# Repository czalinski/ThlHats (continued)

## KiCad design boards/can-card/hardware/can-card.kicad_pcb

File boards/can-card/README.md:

# CAN card: 4 isolated CAN FD

Daughter card in the core's stack (docs/requirements.md 4.5).

- Board: 100 x 100 mm, 2 layers, rev A
- Mounting: 4x M4 stack holes (tools/stack_bus.py), no Pi header
- Stack: J10 logic bus (C1-C4 TX/RX, +3V3, +5V, GND), J11 rack power (+12V,
  GND_RACK, only for CAN1 POWERED); Samtec ESQ stacking sockets on top
- Channels: TI ISOW1044B (basic isolation; ISOW1044 reinforced also fits) each (integrated isolated DC-DC), every bus ground
  floating; MC 1,5/4 terminals: 1 CANH, 2 CANL, 3 GND, 4 +12 V (CAN1 only)
- Jumpers: JP1-JP4 120 R termination; JP5 + JP6 CAN1 POWERED (ties GND_CAN1
  to GND_RACK, feeds +12 V through F10)
- MCU: none (the core's PIC32MK drives the CAN lines)

**Rev B:** each ISOW1044 is replaced by a TI ISO1042 transceiver plus an
isolated 5 V supply (SN6505B, Würth 760390014, LP2985A-50), because the
ISOW1044 and ISOW1044B were out of stock for rev A; rev A can-cards are not
built. See docs/rev-b-changes.md.

## Layout

- `hardware/` KiCad project
  - `gen_schematic.py` bootstrap schematic generator (stop once edited in KiCad)
  - `place.py` outline, holes, placement, domain pours, isolation gaps, TI keep-outs
  - `route.py` routing pipeline (`all` = delete tracks, place, pre, Freerouting, finish)
- `firmware/` none (no MCU on this card)

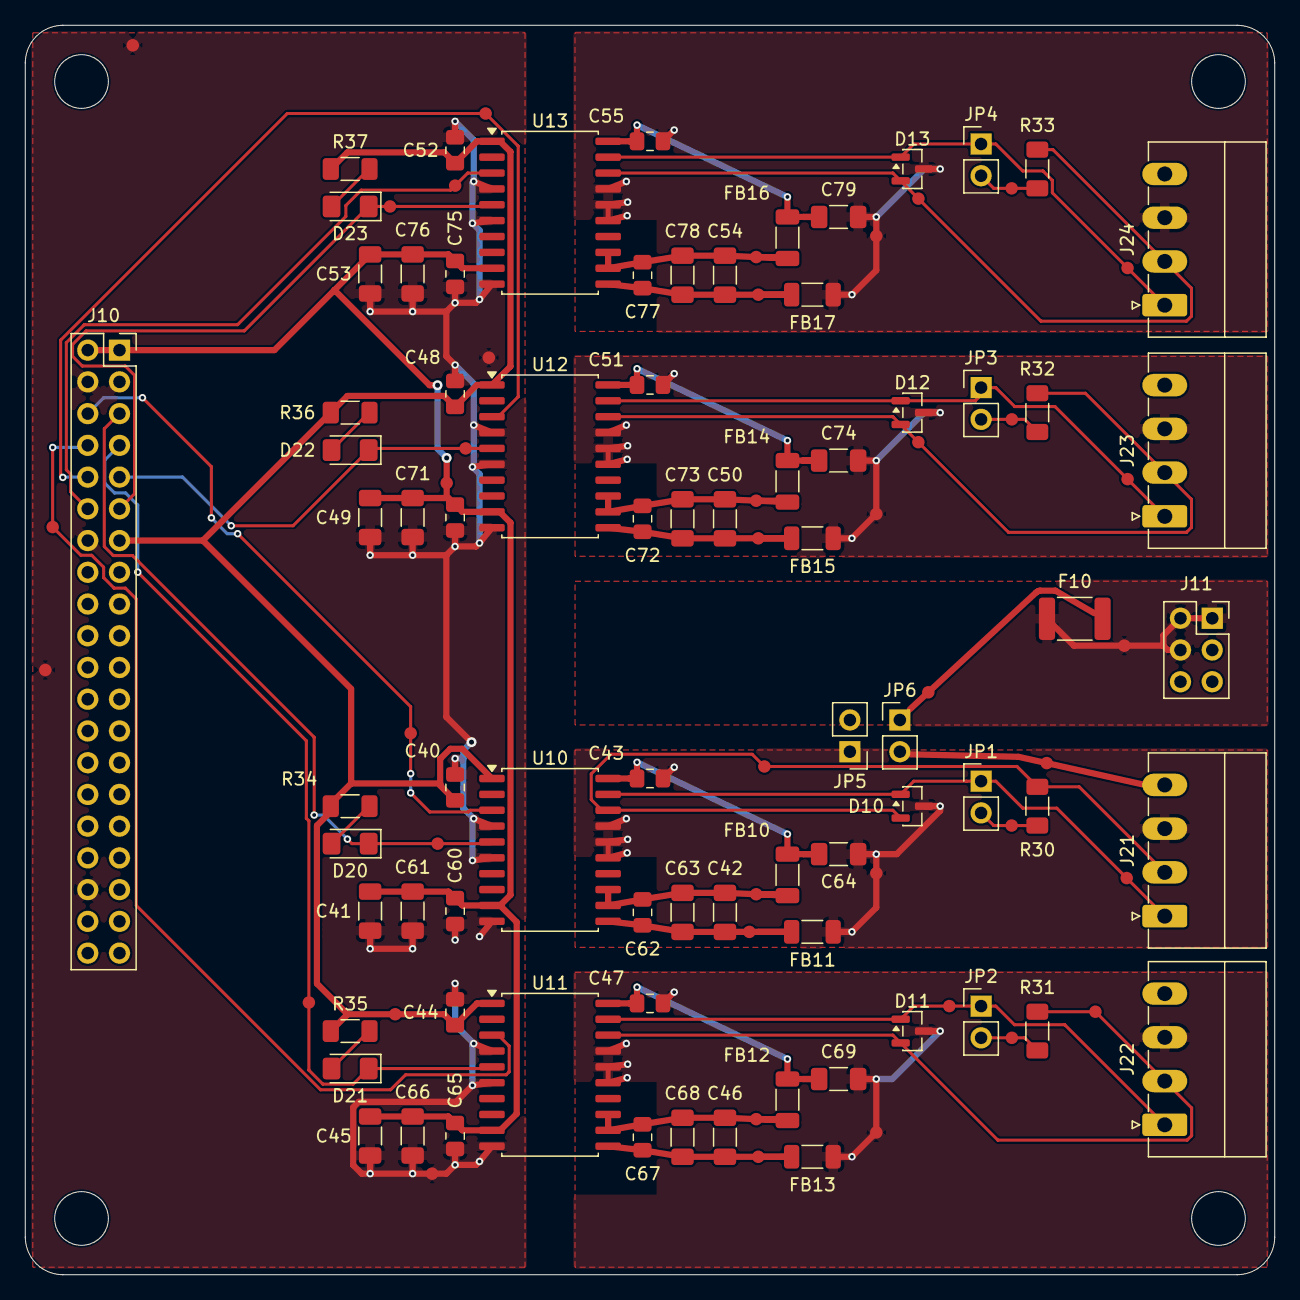
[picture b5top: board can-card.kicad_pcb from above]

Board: 2 copper layers, 100.0 x 100.0 mm, 122 parts (0 on the bottom side), 47 nets.

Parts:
C40, C43, C44, C47, C48, C51, C52, C55: 100nF 50V X7R; C_0805_2012Metric_Pad1.18x1.45mm_HandSolder
C41, C42, C45, C46, C49, C50, C53, C54, C64, C69, C74, C79: 10uF 25V X7R; C_1206_3216Metric_Pad1.33x1.80mm_HandSolder
C60, C62, C65, C67, C70, C72, C75, C77: 10nF 50V X7R; C_0805_2012Metric_Pad1.18x1.45mm_HandSolder
C61, C63, C66, C68, C71, C73, C76, C78: 1uF 50V X7R; C_1206_3216Metric_Pad1.33x1.80mm_HandSolder
D10, D11, D12, D13: NUP2105L; SOT-23
D20, D21, D22, D23: LED yellow; LED_1206_3216Metric_Pad1.42x1.75mm_HandSolder
F10: 2A; Fuse_1812_4532Metric_Pad1.30x3.40mm_HandSolder
FB10, FB11, FB12, FB13, FB14, FB15, FB16, FB17: BLM31PG391SN1L; L_1206_3216Metric_Pad1.22x1.90mm_HandSolder
J10: STACK BUS; PinSocket_2x20_P2.54mm_Vertical
J11: RACK 12V; PinSocket_2x03_P2.54mm_Vertical
J21: CAN1; PhoenixContact_MC_1,5_4-G-3.5_1x04_P3.50mm_Horizontal
J22: CAN2; PhoenixContact_MC_1,5_4-G-3.5_1x04_P3.50mm_Horizontal
J23: CAN3; PhoenixContact_MC_1,5_4-G-3.5_1x04_P3.50mm_Horizontal
J24: CAN4; PhoenixContact_MC_1,5_4-G-3.5_1x04_P3.50mm_Horizontal
JP1, JP2, JP3, JP4: TERM; PinHeader_1x02_P2.54mm_Vertical
JP5: POWERED GND; PinHeader_1x02_P2.54mm_Vertical
JP6: POWERED 12V; PinHeader_1x02_P2.54mm_Vertical
MH1, MH2, MH3, MH4: MountingHole_4.3mm_M4_Standoff7mm
R30, R31, R32, R33: 120R; R_1206_3216Metric_Pad1.30x1.75mm_HandSolder
R34, R35, R36, R37: 1k; R_1206_3216Metric_Pad1.30x1.75mm_HandSolder
TP1, TP10, TP22: pour; TP_Probe_D1.0mm
TP2, TP3, TP4, TP5, TP6, TP7, TP8, TP9, TP11, TP12, TP13, TP14, TP15, TP16, TP17, TP18, TP19, TP20, TP21, TP23, TP24, TP25, TP26, TP27, TP28, TP29, TP30, TP31, TP32, TP33, TP34, TP35, TP36, TP37, TP38, TP39, TP40, TP41: track; TP_Probe_D1.0mm
U10, U11, U12, U13: ISOW1044B; SOIC-20W_7.5x12.8mm_P1.27mm

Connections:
+3V3: C40.1, C44.1, C48.1, C52.1, J10.13, R34.1, R35.1, R36.1, R37.1, TP33.1, U10.1, U11.1, U12.1, U13.1
+5V: C41.1, C45.1, C49.1, C53.1, C60.1, C61.1, C65.1, C66.1, C70.1, C71.1, C75.1, C76.1, J10.1, J10.2, TP12.1, U10.9, U11.9, U12.9, U13.9
+12V: F10.1, J11.1, J11.2, J11.4, TP21.1
/C1RX: D20.1, J10.5, TP27.1, U10.5
/C1TX: J10.6, TP23.1, U10.3
/C2RX: D21.1, J10.7, TP32.1, U11.5
/C2TX: J10.8, TP19.1, U11.3
/C3RX: D22.1, J10.9, TP13.1, U12.5
/C3TX: J10.10, TP2.1, U12.3
/C4RX: D23.1, J10.11, TP3.1, U13.5
/C4TX: J10.12, TP4.1, U13.3
/CANH1: D10.1, J21.1, JP1.1, TP31.1, U10.19
/CANH2: D11.1, J22.1, JP2.1, TP35.1, U11.19
/CANH3: D12.1, J23.1, JP3.1, TP18.1, U12.19
/CANH4: D13.1, J24.1, JP4.1, TP9.1, U13.19
/CANL1: D10.2, J21.2, R30.2, TP24.1, U10.18
/CANL2: D11.2, J22.2, R31.2, TP36.1, U11.18
/CANL3: D12.2, J23.2, R32.2, TP16.1, U12.18
/CANL4: D13.2, J24.2, R33.2, TP7.1, U13.18
/D20_A: D20.2, R34.2
/D21_A: D21.2, R35.2
/D22_A: D22.2, R36.2
/D23_A: D23.2, R37.2
/GND2_1: C42.2, C62.2, C63.2, FB11.1, TP34.1, U10.11
/GND2_2: C46.2, C67.2, C68.2, FB13.1, TP41.1, U11.11
/GND2_3: C50.2, C72.2, C73.2, FB15.1, TP20.1, U12.11
/GND2_4: C54.2, C77.2, C78.2, FB17.1, TP11.1, U13.11
/GND_CAN1: C43.2, C64.2, D10.3, FB11.2, J21.3, JP5.1, TP29.1, U10.15, U10.16, U10.17
/GND_CAN2: C47.2, C69.2, D11.3, FB13.2, J22.3, TP38.1, U11.15, U11.16, U11.17
/GND_CAN3: C51.2, C74.2, D12.3, FB15.2, J23.3, TP15.1, U12.15, U12.16, U12.17
/GND_CAN4: C55.2, C79.2, D13.3, FB17.2, J24.3, TP6.1, U13.15, U13.16, U13.17
/GND_RACK: J11.3, J11.5, J11.6, JP5.2
/TERM1: JP1.2, R30.1, TP30.1
/TERM2: JP2.2, R31.1, TP39.1
/TERM3: JP3.2, R32.1, TP17.1
/TERM4: JP4.2, R33.1, TP8.1
/V12_CAN1: J21.4, JP6.2, TP26.1
/V12_F10: F10.2, JP6.1, TP25.1
/VCAN1: C43.1, C64.1, FB10.2, U10.20
/VCAN2: C47.1, C69.1, FB12.2, U11.20
/VCAN3: C51.1, C74.1, FB14.2, U12.20
/VCAN4: C55.1, C79.1, FB16.2, U13.20
/VISO1: C42.1, C62.1, C63.1, FB10.1, TP28.1, U10.12, U10.13
/VISO2: C46.1, C67.1, C68.1, FB12.1, TP37.1, U11.12, U11.13
/VISO3: C50.1, C72.1, C73.1, FB14.1, TP14.1, U12.12, U12.13
/VISO4: C54.1, C77.1, C78.1, FB16.1, TP5.1, U13.12, U13.13
GND: C40.2, C41.2, C44.2, C45.2, C48.2, C49.2, C52.2, C53.2, C60.2, C61.2, C65.2, C66.2, C70.2, C71.2, C75.2, C76.2, J10.3, J10.4, J10.14, J10.36, TP1.1, TP10.1, TP22.1, TP40.1, U10.4, U10.6, U10.10, U11.4, U11.6, U11.10, U12.4, U12.6, U12.10, U13.4, U13.6, U13.10

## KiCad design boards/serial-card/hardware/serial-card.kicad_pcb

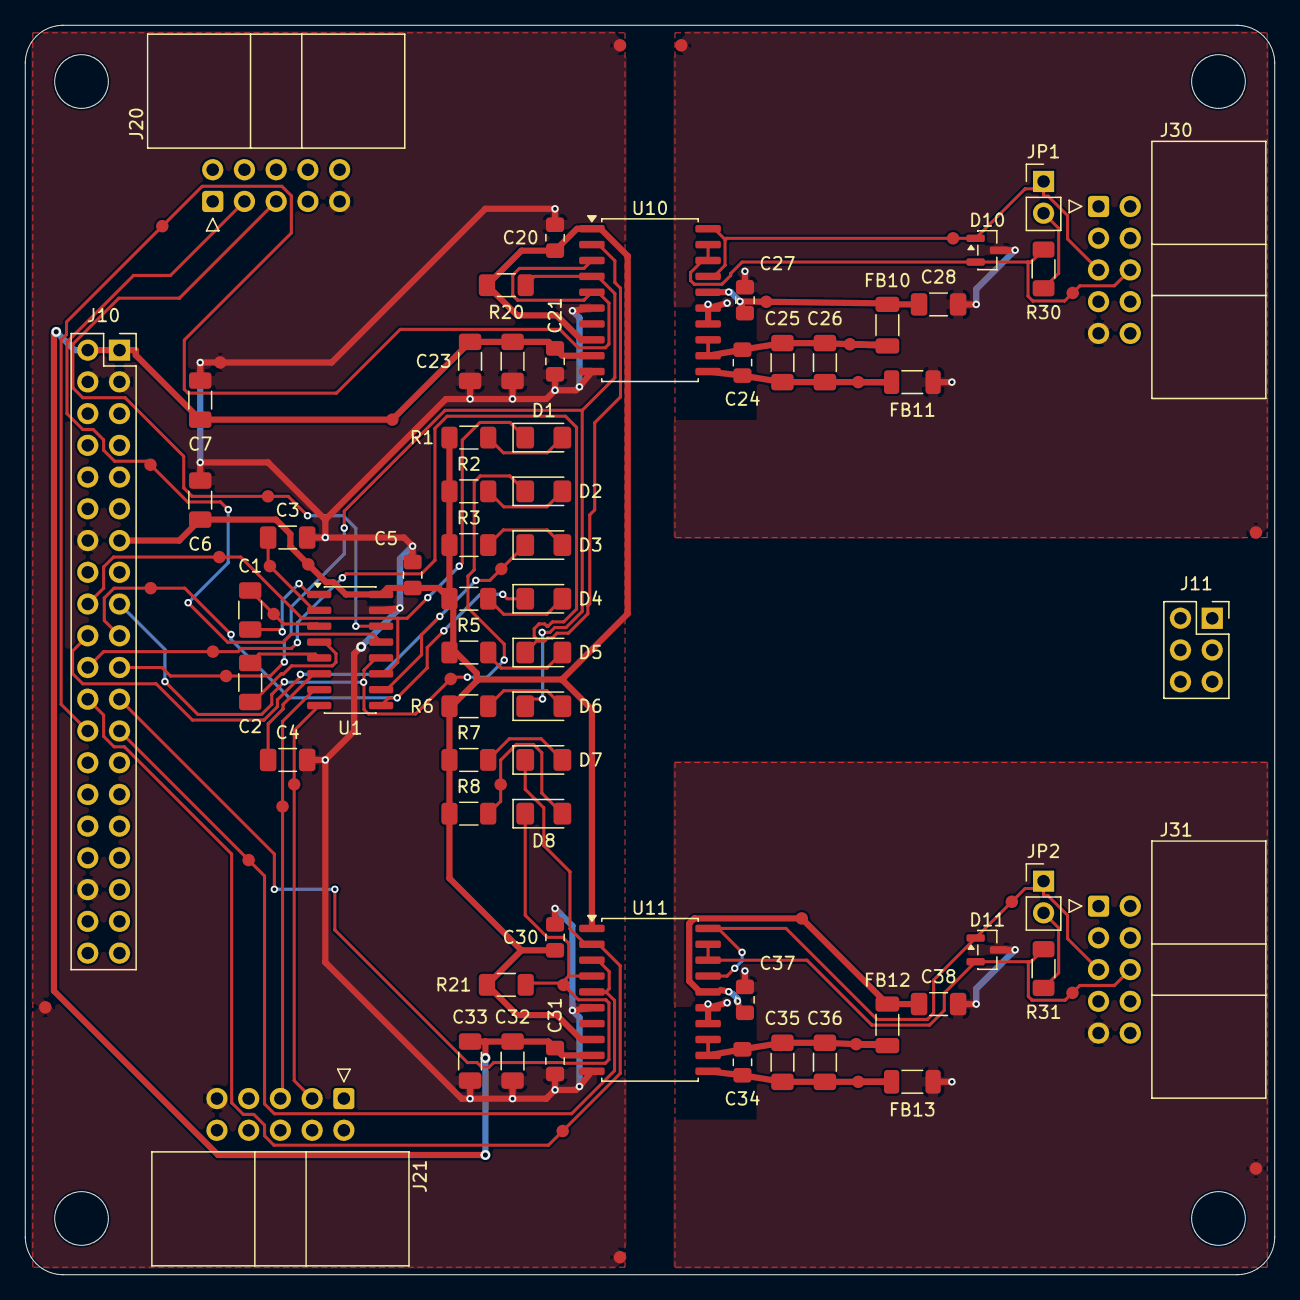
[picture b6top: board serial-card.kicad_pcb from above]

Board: 2 copper layers, 100.0 x 100.0 mm, 102 parts (0 on the bottom side), 45 nets.

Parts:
C1, C2, C3, C4: 100nF 50V X7R; C_1206_3216Metric_Pad1.33x1.80mm_HandSolder
C5, C20, C27, C30, C37: 100nF 50V X7R; C_0805_2012Metric_Pad1.18x1.45mm_HandSolder
C6, C7, C23, C26, C28, C33, C36, C38: 10uF 25V X7R; C_1206_3216Metric_Pad1.33x1.80mm_HandSolder
C21, C24, C31, C34: 10nF 50V X7R; C_0805_2012Metric_Pad1.18x1.45mm_HandSolder
C22, C25, C32, C35: 1uF 50V X7R; C_1206_3216Metric_Pad1.33x1.80mm_HandSolder
D1, D3, D5, D7: LED green; LED_1206_3216Metric_Pad1.42x1.75mm_HandSolder
D2, D4, D6, D8: LED yellow; LED_1206_3216Metric_Pad1.42x1.75mm_HandSolder
D10, D11: SM712; SOT-23
FB10, FB11, FB12, FB13: BLM31PG391SN1L; L_1206_3216Metric_Pad1.22x1.90mm_HandSolder
J10: STACK BUS; PinSocket_2x20_P2.54mm_Vertical
J11: RACK 12V; PinSocket_2x03_P2.54mm_Vertical
J20: RS-232 1; Amphenol_T821110A1R100CEU_2x05_P2.54mm_Horizontal
J21: RS-232 2; Amphenol_T821110A1R100CEU_2x05_P2.54mm_Horizontal
J30: RS-485 3; Amphenol_T821110A1R100CEU_2x05_P2.54mm_Horizontal
J31: RS-485 4; Amphenol_T821110A1R100CEU_2x05_P2.54mm_Horizontal
JP1, JP2: TERM; PinHeader_1x02_P2.54mm_Vertical
MH1, MH2, MH3, MH4: MountingHole_4.3mm_M4_Standoff7mm
R1, R2, R3, R4, R5, R6, R7, R8: 1k; R_1206_3216Metric_Pad1.30x1.75mm_HandSolder
R20, R21: 10k; R_1206_3216Metric_Pad1.30x1.75mm_HandSolder
R30, R31: 120R; R_1206_3216Metric_Pad1.30x1.75mm_HandSolder
TP1, TP2, TP19, TP27, TP35, TP36: pour; TP_Probe_D1.0mm
TP3, TP4, TP5, TP6, TP7, TP8, TP9, TP10, TP11, TP12, TP13, TP14, TP15, TP16, TP17, TP18, TP20, TP21, TP22, TP23, TP24, TP25, TP26, TP28, TP29, TP30, TP31, TP32, TP33, TP34: track; TP_Probe_D1.0mm
U1: ST3232B; SOIC-16_3.9x9.9mm_P1.27mm
U10, U11: ISOW1432; SOIC-20W_7.5x12.8mm_P1.27mm

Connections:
+3V3: C5.1, C6.1, C20.1, C30.1, J10.13, R1.1, R2.1, R3.1, R4.1, R5.1, R6.1, R7.1, R8.1, R20.1, R21.1, TP17.1, U1.16, U10.1, U10.8, U11.1, U11.8
+5V: C7.1, C21.1, C22.1, C23.1, C31.1, C32.1, C33.1, J10.1, J10.2, TP12.1, U10.9, U11.9
/C1N: C1.2, TP16.1, U1.3
/C1P: C1.1, U1.1
/C2N: C2.2, U1.5
/C2P: C2.1, U1.4
/D1_A: D1.2, R1.2
/D2_A: D2.2, R2.2
/D3_A: D3.2, R3.2
/D4_A: D4.2, R4.2
/D5_A: D5.2, R5.2
/D6_A: D6.2, R6.2
/D7_A: D7.2, R7.2
/D8_A: D8.2, R8.2, TP26.1
/DE1: J10.26, TP3.1, U10.3, U10.5
/DE2: J10.25, TP23.1, U11.3, U11.5
/DN3: D10.2, J30.6, R30.2, TP9.1, U10.18, U10.19
/DN4: D11.2, J31.6, R31.2, TP31.1, U11.18, U11.19
/DP3: D10.1, J30.5, JP1.1, TP4.1, U10.17, U10.20
/DP4: D11.1, J31.5, JP2.1, TP30.1, U11.17, U11.20
/GND2_3: C24.2, C25.2, C26.2, FB11.1, TP8.1, U10.11
/GND2_4: C34.2, C35.2, C36.2, FB13.1, TP34.1, U11.11
/GND_485_3: C27.2, C28.2, D10.3, FB11.2, J30.9, TP2.1, TP19.1, U10.14, U10.15
/GND_485_4: C37.2, C38.2, D11.3, FB13.2, J31.9, TP36.1, U11.14, U11.15
/RXD1: J20.3, TP10.1, U1.13
/RXD2: J21.3, TP25.1, U1.8
/TERM3: JP1.2, R30.1
/TERM4: JP2.2, R31.1
/TXD1: J20.5, TP11.1, U1.14
/TXD2: J21.5, TP24.1, U1.7
/U2RX: D2.1, J10.17, TP22.1, U1.12
/U2TX: D1.1, J10.18, TP14.1, U1.11
/U3RX: D4.1, J10.19, TP13.1, U1.9
/U3TX: D3.1, J10.20, TP18.1, U1.10
/U4RX: D6.1, J10.21, R20.2, TP21.1, U10.4
/U4TX: D5.1, J10.22, TP20.1, U10.2
/U5RX: D8.1, J10.23, R21.2, TP28.1, U11.4
/U5TX: D7.1, J10.24, TP32.1, U11.2
/V485_3: C27.1, C28.1, FB10.2, TP6.1, U10.16
/V485_4: C37.1, C38.1, FB12.2, TP29.1, U11.16
/VISO3: C24.1, C25.1, C26.1, FB10.1, TP7.1, U10.12, U10.13
/VISO4: C34.1, C35.1, C36.1, FB12.1, TP33.1, U11.12, U11.13
/VSN: C4.1, U1.6
/VSP: C3.1, TP15.1, U1.2
GND: C3.2, C4.2, C5.2, C6.2, C7.2, C20.2, C21.2, C22.2, C23.2, C30.2, C31.2, C32.2, C33.2, J10.3, J10.4, J10.14, J10.36, J20.9, J21.9, TP1.1, TP5.1, TP27.1, TP35.1, U1.15, U10.6, U10.10, U11.6, U11.10

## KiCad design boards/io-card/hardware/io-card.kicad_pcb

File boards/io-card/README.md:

# IO card: relays, GPIO, differential AI, analog out

The "LabJack light" daughter card in the core's stack (docs/requirements.md
4.1 and 4.5). It has no MCU: the core's PIC32MK drives RLY1-4 and GPIO1-4 and
reads the analog legs on its ADC through the stack bus, and sets the analog
outputs over the bus's I2C1.

- Board: 100 x 100 mm, 2 layers, rev A.
- Mounting: 4x M4 stack holes (tools/stack_bus.py), no Pi header
  (`board.json` opts out).
- Stack: J10 logic bus (left edge) and J11 rack power (right edge), Samtec
  ESQ stacking sockets on top, as on the can-card. Every part stays under the
  next card, about 11 mm up (ESQ-120-14 body).

| Block | Circuit | Terminal |
|---|---|---|
| Relay drivers 1-4 | Drive **external** relay coils. 2 × Panasonic AQW212 PhotoMOS. The LED side runs on LOGIC: RLYn → 470R → LED. The contacts source V_RLY to OUTn, and the coil returns to 0 V next to it. Coil supply on JP1: 1-2 = rack +12 V (J11), 2-3 = external supply up to 24 V on J30 9/10. Both go through F30 (1.1 A, 33 V). Each output has a 1N4148W flyback diode and a red LED. The failsafe timeout is set by the host per `RLY` command and enforced by the core firmware. | **J30** bottom edge, MC 1,5/10-G-3,5: 1/2 OUT1 / 0 V … 7/8 OUT4 / 0 V, 9/10 external coil supply + / 0 V |
| GPIO 1-4 | 3.3 V straight from core pins, with 330R in series and a BAT54S clamp. Not 24 V tolerant. | **J40** top edge, MC 1,5/12-G-3,5: 1/2 IO1 / GND … 7/8 IO4 / GND |
| AO 1-4 (2026-10-10) | 0-10 V, 10 mA each, in the RACK domain: powered from rack +12 V, 0 V = GND_RACK (shared by all four and the relay returns). I2C1 from the bus crosses U90 (ISO1540) to U92 (MCP4728 quad 12-bit DAC at 0x60, internal 2.048 V reference x 2), then U93 (OPA4171) x 2.5 = 10.24 V full scale. 47R inside the loop (feedback from the terminal side) + 1 nF from the amplifier output for cable capacitance; BAT54S clamp to +12V / GND_RACK. U91 (MC78L05) makes 5 V for the DAC and the isolator's rack side. Needs the rack supply at 11 V or more for 10 V at 10 mA. | **J50** right edge, MC 1,5/8-G-3,5: 1/2 AO1 / 0 V … 7/8 AO4 / 0 V |
| AI 1-2 | Differential, ±116 V per input, 10 MΩ per input. Each leg is 10M / 130k to VMID_F, with 100 nF across the 130k and a BAT54S clamp. The core subtracts the two legs. VMID from the core arrives through R88 1k + C85 100 nF (VMID_F), because the core's OA5 is rated for only 32 pF of load. | J40 9/10 AI1+ / AI1-, 11/12 AI2+ / AI2- |

Plugs: Phoenix FMC 1,5/10-ST-3,5 and FMC 1,5/12-ST-3,5 (push-in, 7.8 mm).
The MC headers are 7.7 mm tall. The double-level SPTD terminals from the
first schematic are 24.2 mm tall and do not fit in the stack.

## Layout

- LOGIC: the top band (J40, GPIO clamps, AI dividers) and the left side
  (J10, decoupling, relay LED resistors).
- RACK: the lower-right block (J11, JP1, F30, C70/C71, flyback diodes, LEDs,
  J30).
- RACK also takes the top-right corner (x > 61.5 mm) for the analog outputs:
  the isolator, U91-U93, each channel's parts in a row beside its J50 pair.
- K1/K2 and U90 straddle a 2 mm copper-free gap on both layers. They are
  the only LOGIC | RACK crossings (1500 Vrms and 2500 Vrms, functional
  isolation).
- Ground pours on both layers in each domain.
- The AI terminal nets (`/AIN*`) are in net class HV, with a 0.8 mm
  clearance (IPC-2221B B4 needs 0.6 mm for 101-150 V).
- The MCP4728's nets are in net class Fine (0.2 mm tracks, 0.15 mm
  clearance) and a DRC rule allows its 0.15 mm pad gaps (MSOP-10, 0.5 mm
  pitch). Its pins and the four DAC-to-amplifier connections are routed by
  `route.py` (`dac_fanout`); Freerouting did not get through the pitch
  reliably.

## Build files

- `hardware/gen_schematic.py`: generates the schematic (A2 sheet: the
  analog outputs are in the band below the original A3 area). Stop using it
  once the schematic is edited in KiCad.
- `hardware/place.py`: outline, holes, placement, pours and the isolation
  gap. It can be rerun and leaves tracks alone.
- `hardware/route.py pre|auto|finish|all`: ground fan-out, Freerouting, then
  finishing. **Do not rerun `pre` or `all` on a hand-edited board**: they
  start over. `route.py ao` routed the analog outputs onto the routed board:
  it locks the existing tracks, fans out the new ground pads, pre-routes the
  DAC, runs Freerouting, removes the fragments Freerouting leaves on
  already-routed nets, and unlocks. Freerouting is not deterministic; check
  DRC after each run.

## Status (2026-10-10)

Analog outputs added: schematic, placement and routing. `tools/check_board.py`
is clean (ERC, DRC with schematic parity). The original routing is
unchanged, track for track. Core firmware 0.5 has the `AO` command
(boards/core/firmware/PROTOCOL.md); not yet tested on hardware.

## Status (2026-10-09)

Placed and routed. `tools/check_board.py` is clean: ERC, DRC and schematic
parity, with no warnings. References were tidied with `tools/silk_tidy.py`; D57's appears on the Fab layer only, because there was no clear silkscreen spot.
Next: io-card commands in the core firmware (RLY, GPIO, AI, and OA5 for
VMID).

Open items:

- Confirm the mated FMC plug height against the stack on the Phoenix
  drawing.
- There is no reverse-polarity protection on the external coil supply. If
  it is reversed, an output that is on lets its flyback diode short the
  supply through F30, which trips. Outputs that are off block it: the
  AQW212 is the GU AC/DC type (back-to-back MOSFETs; checked 2026-10-11).

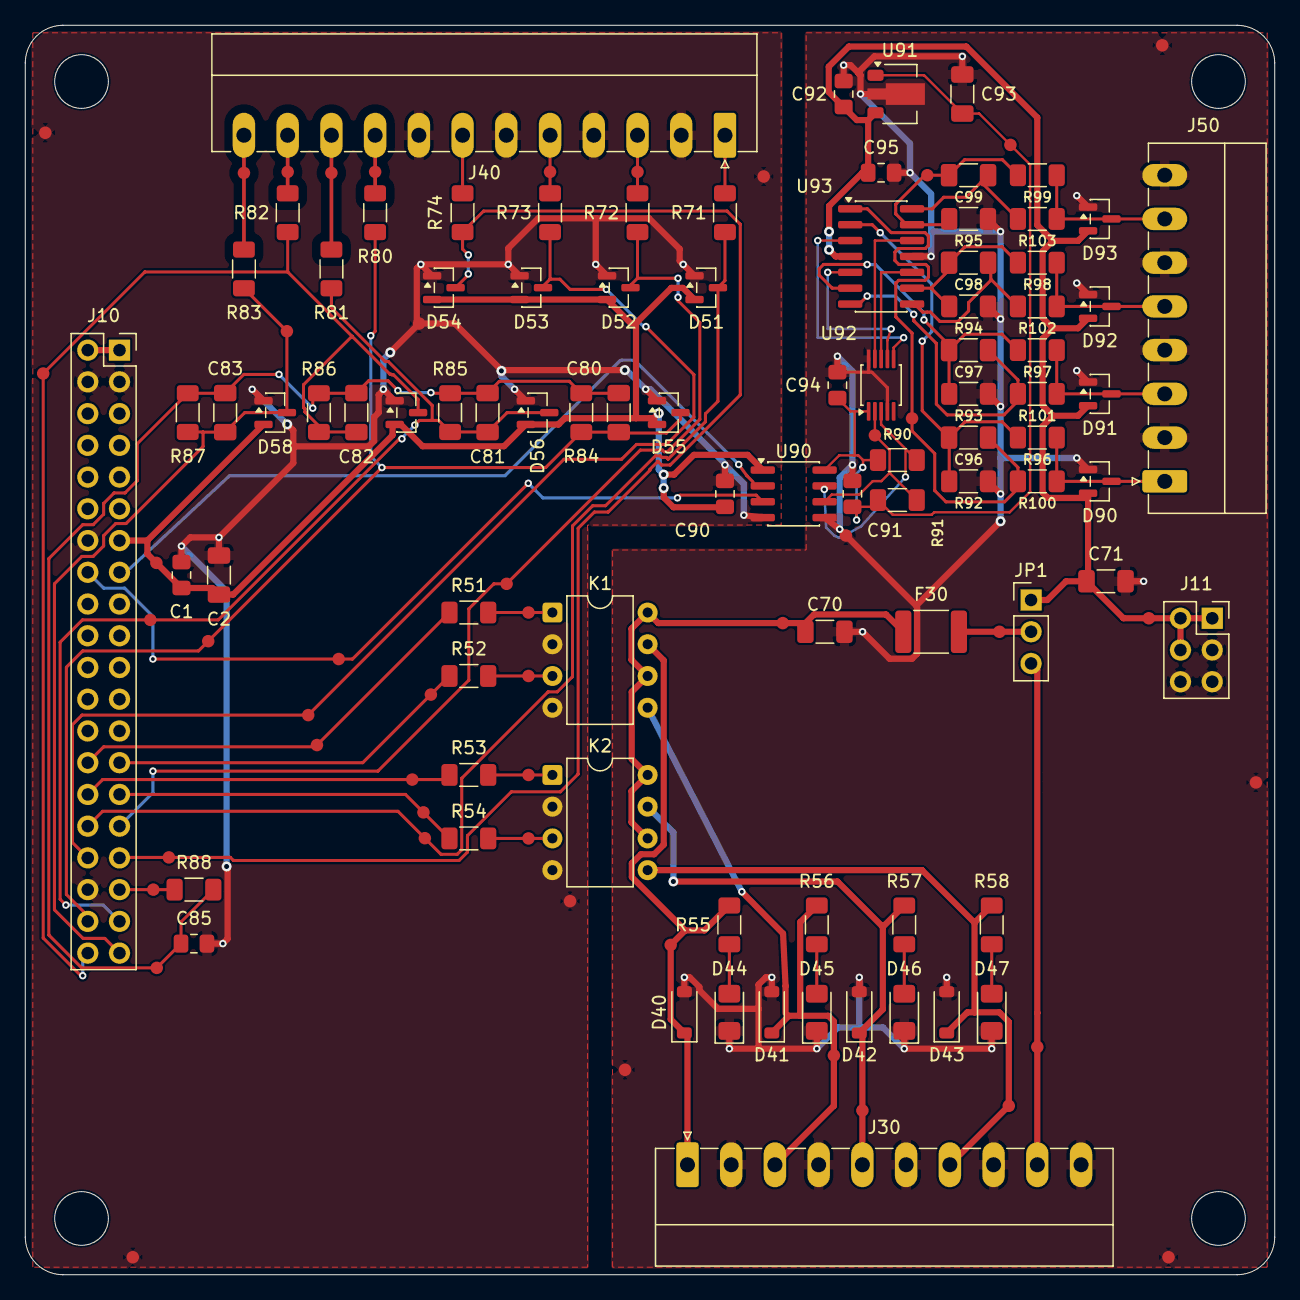
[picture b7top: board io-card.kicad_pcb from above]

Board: 2 copper layers, 100.0 x 100.0 mm, 139 parts (0 on the bottom side), 63 nets.

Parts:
C1, C85, C90, C91, C92, C94, C95: 100nF 50V X7R; C_0805_2012Metric_Pad1.18x1.45mm_HandSolder
C2, C71, C93: 10uF 25V X7R; C_1206_3216Metric_Pad1.33x1.80mm_HandSolder
C70: 4.7uF 50V X7R; C_1206_3216Metric_Pad1.33x1.80mm_HandSolder
C80, C81, C82, C83: 100nF 50V X7R; C_1206_3216Metric_Pad1.33x1.80mm_HandSolder
C96, C97, C98, C99: 1nF 50V C0G; C_1206_3216Metric_Pad1.33x1.80mm_HandSolder
D40, D41, D42, D43: 1N4148W; D_SOD-123
D44, D45, D46, D47: LED red; LED_1206_3216Metric_Pad1.42x1.75mm_HandSolder
D51, D52, D53, D54, D55, D56, D57, D58, D90, D91, D92, D93: BAT54S; SOT-23
F30: 1.1A 33V; Fuse_1812_4532Metric_Pad1.30x3.40mm_HandSolder
J10: STACK BUS; PinSocket_2x20_P2.54mm_Vertical
J11: RACK 12V; PinSocket_2x03_P2.54mm_Vertical
J30: RELAY; PhoenixContact_MC_1,5_10-G-3.5_1x10_P3.50mm_Horizontal
J40: IO; PhoenixContact_MC_1,5_12-G-3.5_1x12_P3.50mm_Horizontal
J50: ANALOG OUT; PhoenixContact_MC_1,5_8-G-3.5_1x08_P3.50mm_Horizontal
JP1: COIL SUPPLY; PinHeader_1x03_P2.54mm_Vertical
K1, K2: AQW212; DIP-8_W7.62mm
MH1, MH2, MH3, MH4: MountingHole_4.3mm_M4_Standoff7mm
R51, R52, R53, R54: 470R; R_1206_3216Metric_Pad1.30x1.75mm_HandSolder
R55, R56, R57, R58, R90, R91: 4.7k; R_1206_3216Metric_Pad1.30x1.75mm_HandSolder
R71, R72, R73, R74: 330R; R_1206_3216Metric_Pad1.30x1.75mm_HandSolder
R80, R81, R82, R83: 10M; R_1206_3216Metric_Pad1.30x1.75mm_HandSolder
R84, R85, R86, R87: 130k; R_1206_3216Metric_Pad1.30x1.75mm_HandSolder
R88: 1k; R_1206_3216Metric_Pad1.30x1.75mm_HandSolder
R92, R93, R94, R95: 10k 0.1%; R_1206_3216Metric_Pad1.30x1.75mm_HandSolder
R96, R97, R98, R99: 15k 0.1%; R_1206_3216Metric_Pad1.30x1.75mm_HandSolder
R100, R101, R102, R103: 47R; R_1206_3216Metric_Pad1.30x1.75mm_HandSolder
TP1, TP3, TP10, TP38, TP40, TP42, TP47, TP48: pour; TP_Probe_D1.0mm
TP2, TP4, TP5, TP6, TP7, TP8, TP9, TP11, TP12, TP13, TP14, TP15, TP16, TP17, TP18, TP19, TP20, TP21, TP22, TP23, TP24, TP25, TP26, TP27, TP28, TP29, TP30, TP31, TP32, TP33, TP34, TP35, TP36, TP37, TP39, TP41, TP43, TP44, TP45, TP46: track; TP_Probe_D1.0mm
U90: ISO1540; SOIC-8_3.9x4.9mm_P1.27mm
U91: MC78L05; SOT-89-3
U92: MCP4728; MSOP-10_3x3mm_P0.5mm_Pad0.30
U93: OPA4171; SOIC-14_3.9x8.7mm_P1.27mm

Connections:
+3V3: C1.1, C2.1, C90.1, D51.2, D52.2, D53.2, D54.2, D55.2, D56.2, D57.2, D58.2, J10.13, TP18.1, U90.1
+5V: J10.1, J10.2
+12V: C71.1, C92.1, C95.1, D90.2, D91.2, D92.2, D93.2, J11.1, J11.2, J11.4, JP1.1, TP25.1, U91.3, U93.4
/AI1N: C81.1, D56.3, J10.37, R81.2, R85.1, TP17.1
/AI1P: C80.1, D55.3, J10.38, R80.2, R84.1, TP19.1
/AI2N: C83.1, D58.3, J10.39, R83.2, R87.1, TP13.1
/AI2P: C82.1, D57.3, J10.40, R82.2, R86.1, TP12.1
/AIN1N: J40.10, R81.1, TP6.1
/AIN1P: J40.9, R80.1, TP7.1
/AIN2N: J40.12, R83.1, TP4.1
/AIN2P: J40.11, R82.1, TP5.1
/AO1: D90.3, J50.1, R96.2, R100.2
/AO2: D91.3, J50.3, R97.2, R101.2
/AO3: D92.3, J50.5, R98.2, R102.2
/AO4: D93.3, J50.7, R99.2, R103.2
/AO_SCL: R91.2, TP15.1, U90.6, U92.2
/AO_SDA: R90.2, U90.7, U92.3
/D44_A: D44.2, R55.2
/D45_A: D45.2, R56.2
/D46_A: D46.2, R57.2
/D47_A: D47.2, R58.2
/DAC1: U92.6, U93.3
/DAC2: U92.7, U93.5
/DAC3: U92.8, U93.10
/DAC4: U92.9, U93.12
/GND_RACK: C70.2, C71.2, C91.2, C92.2, C93.2, C94.2, C95.2, D40.2, D41.2, D42.2, D43.2, D44.1, D45.1, D46.1, D47.1, D90.1, D91.1, D92.1, D93.1, J11.3, J11.5, J11.6, J30.2, J30.4, J30.6, J30.8, J30.10, J50.2, J50.4, J50.6, J50.8, R92.2, R93.2, R94.2, R95.2, TP3.1, TP23.1, TP38.1, TP42.1, TP48.1, U90.5, U91.2, U92.4, U92.10, U93.11
/GPIO1: D51.3, J10.32, R71.1, TP35.1
/GPIO2: D52.3, J10.31, R72.1, TP20.1
/GPIO3: D53.3, J10.34, R73.1, TP26.1
/GPIO4: D54.3, J10.33, R74.1, TP32.1
/IO1: J40.1, R71.2
/IO2: J40.3, R72.2, TP9.1
/IO3: J40.5, R73.2, TP8.1
/IO4: J40.7, R74.2
/OUT1: D40.1, J30.1, K1.7, R55.1, TP41.1
/OUT2: D41.1, J30.3, K1.5, R56.1, TP43.1
/OUT3: D42.1, J30.5, K2.7, R57.1, TP44.1
/OUT4: D43.1, J30.7, K2.5, R58.1, TP45.1
/RLED1: K1.1, R51.2, TP21.1
/RLED2: K1.3, R52.2, TP30.1
/RLED3: K2.1, R53.2, TP37.1
/RLED4: K2.3, R54.2, TP36.1
/RLY1: J10.28, R51.1, TP27.1
/RLY2: J10.27, R52.1, TP29.1
/RLY3: J10.30, R53.1, TP33.1
/RLY4: J10.29, R54.1, TP34.1
/SCL: J10.16, TP28.1, U90.3
/SDA: J10.15, U90.2
/V5_AO: C91.1, C93.1, C94.1, R90.1, R91.1, TP2.1, U90.8, U91.1, U92.1
/VMID: J10.35, R88.1, TP31.1
/VMID_F: C80.2, C81.2, C82.2, C83.2, C85.1, R84.2, R85.2, R86.2, R87.2, R88.2, TP39.1
/V_COIL_EXT: J30.9, JP1.3, TP46.1
/V_COIL_SEL: F30.1, JP1.2, TP24.1
/V_RLY: C70.1, F30.2, K1.6, K1.8, K2.6, K2.8, TP22.1
GND: C1.2, C2.2, C85.2, C90.2, D51.1, D52.1, D53.1, D54.1, D55.1, D56.1, D57.1, D58.1, J10.3, J10.4, J10.14, J10.36, J40.2, J40.4, J40.6, J40.8, K1.2, K1.4, K2.2, K2.4, TP1.1, TP10.1, TP14.1, TP40.1, TP47.1, U90.4
unnamed: C96.2, R100.1, TP16.1, U93.1
unnamed: C97.2, R101.1, U93.7
unnamed: C98.2, R102.1, U93.8
unnamed: C99.2, R103.1, U93.14
unnamed: C96.1, R92.1, R96.1, U93.2
unnamed: C97.1, R93.1, R97.1, U93.6
unnamed: C98.1, R94.1, R98.1, U93.9
unnamed: C99.1, R95.1, R99.1, TP11.1, U93.13

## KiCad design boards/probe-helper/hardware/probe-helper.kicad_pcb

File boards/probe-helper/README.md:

# Probe helper: ADS1263 HAT adapter

Resistor/clamp board for the probe meter: Raspberry Pi + Waveshare
High-Precision AD HAT (TI ADS1263), run by `tools/probe_ads1263.py`.
Circuit, parts, assembly and bring-up: `docs/probe-helper-pi.md`.

- Board: 65 x 46 mm, 2 layers, rev A, all through-hole (hand assembly)
- J1: 13 right-angle pins at 3.5 mm on the **bottom** side, into the HAT's
  13-way screw terminal (AVDD ... COM)
- J2: 2x5 box header, ribbon to the HAT's pass-through Pi pins 31-40
- J3: probe leads A (red) and B (black)
- Mounting (`board.json`: not on the HAT pattern): tabs MH1/MH2 over the HAT's
  terminal-side holes (about 4 mm spacers), MH3/MH4 on the Pi's far holes
  (Pi y 52.5). The board sits above the HAT.

## Layout

- `hardware/gen_schematic.py` schematic generator (bootstrap)
- `hardware/place.py` outline, holes, placement, pours, silkscreen (rerunnable)
- routing: `tools/freeroute.py boards/probe-helper --skip GND`
- `firmware/`: none; the Pi runs `tools/probe_ads1263.py`

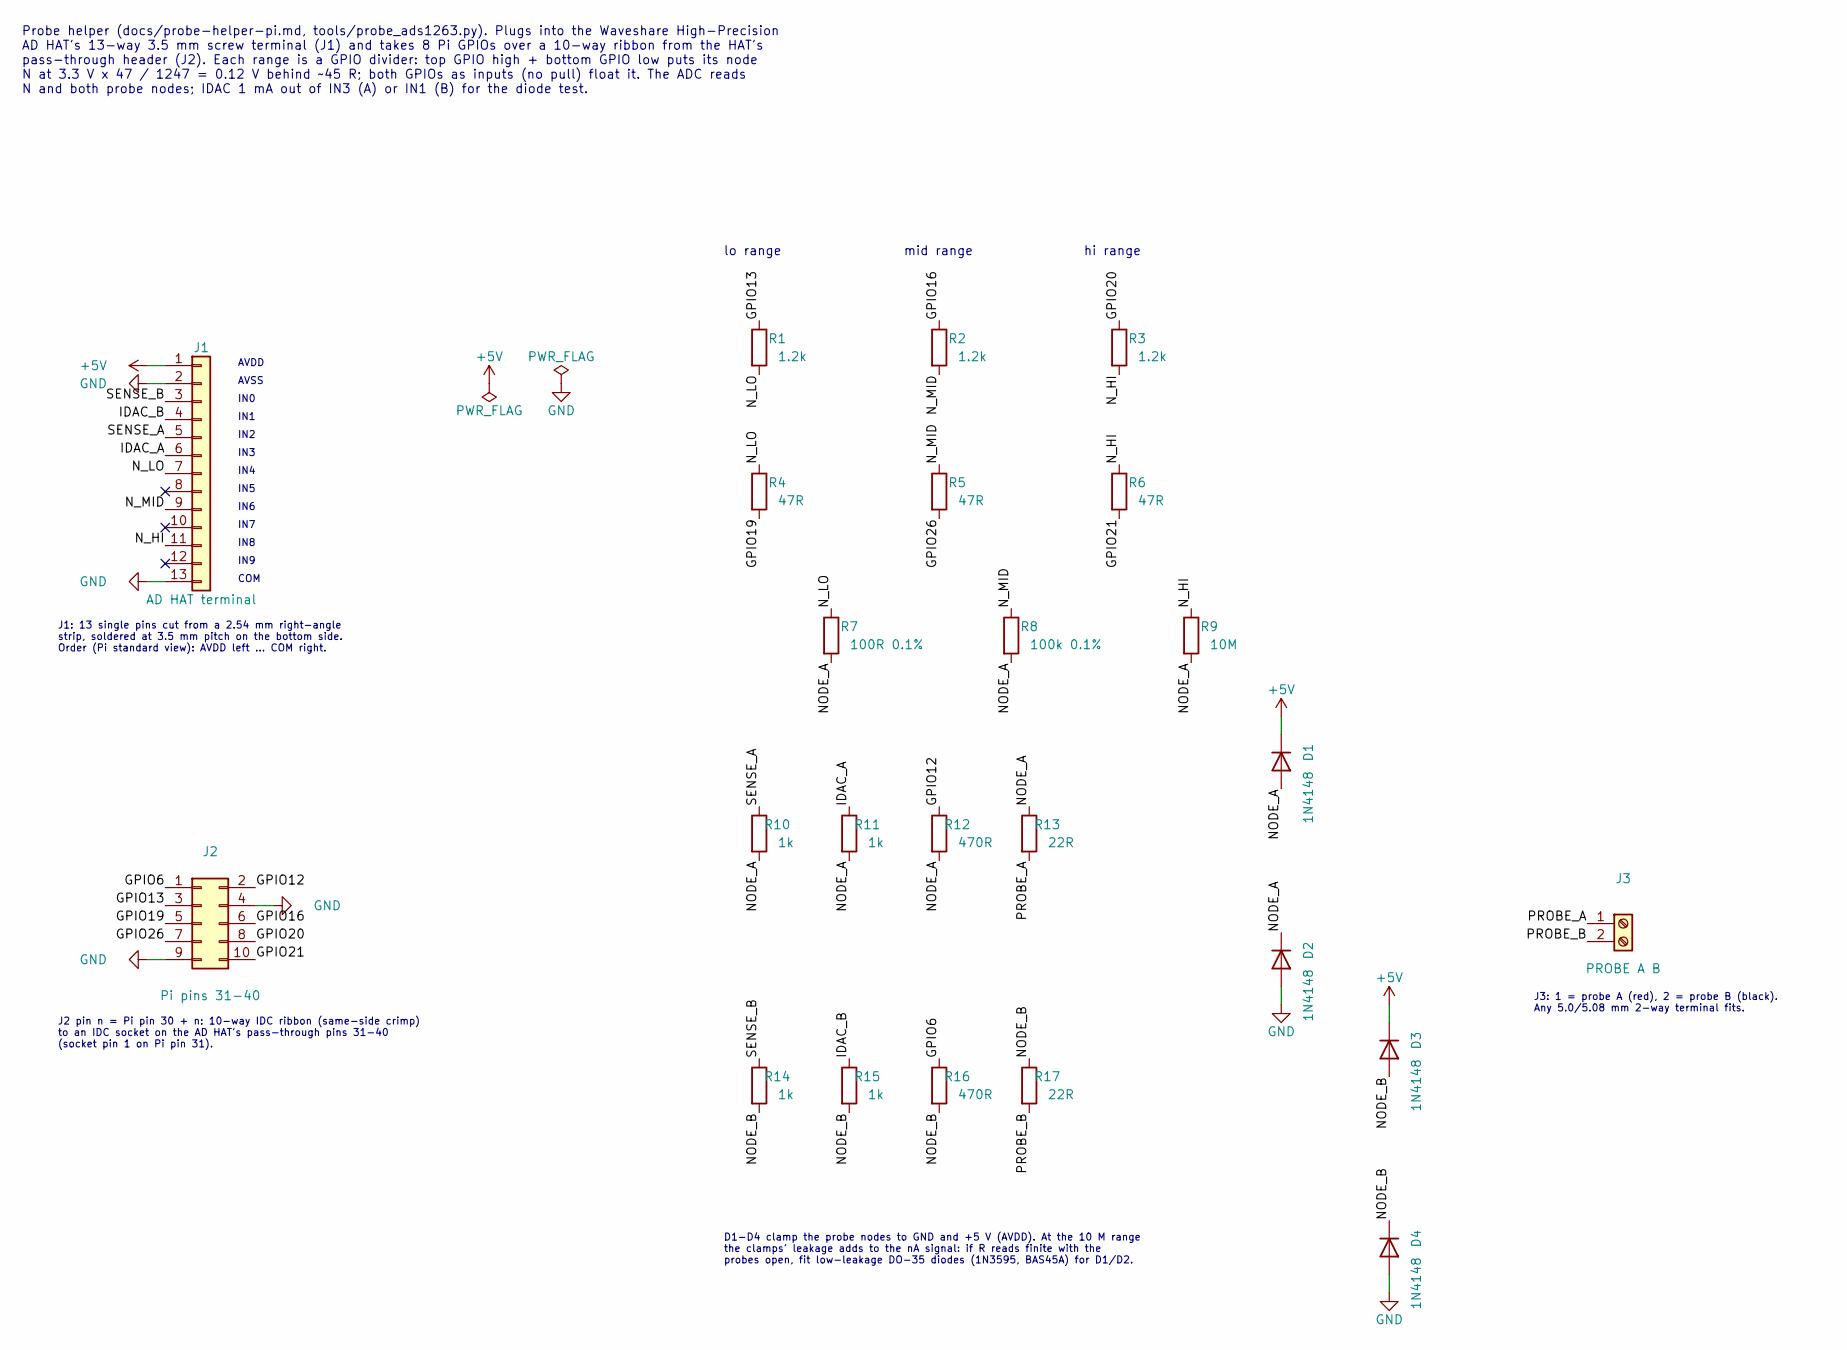
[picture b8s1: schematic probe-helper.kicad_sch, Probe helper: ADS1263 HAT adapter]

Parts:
D1, D2, D3, D4: 1N4148; D_DO-35_SOD27_P7.62mm_Horizontal; MPN 1N4148
J1: AD HAT terminal; PinHeader_1x13_P3.50mm_Horizontal; MPN 68016-136HLF
J2: Pi pins 31-40; IDC-Header_2x05_P2.54mm_Vertical; MPN 61201021621
J3: PROBE A B; TerminalBlock_Phoenix_MKDS-1,5-2-5.08_1x02_P5.08mm_Horizont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; MPN 1715721
R1, R2, R3: 1.2k; R_Axial_DIN0207_L6.3mm_D2.5mm_P10.16mm_Horizontal; MPN MFR-25FBF52-1K2
R4, R5, R6: 47R; R_Axial_DIN0207_L6.3mm_D2.5mm_P10.16mm_Horizontal; MPN MFR-25FBF52-47R
R7: 100R 0.1%; R_Axial_DIN0207_L6.3mm_D2.5mm_P10.16mm_Horizontal; MPN MFP-25BRD52-100R
R8: 100k 0.1%; R_Axial_DIN0207_L6.3mm_D2.5mm_P10.16mm_Horizontal; MPN MFP-25BRD52-100K
R9: 10M; R_Axial_DIN0207_L6.3mm_D2.5mm_P10.16mm_Horizontal; MPN RNF14FTD10M0
R10, R11, R14, R15: 1k; R_Axial_DIN0207_L6.3mm_D2.5mm_P10.16mm_Horizontal; MPN MFR-25FBF52-1K
R12, R16: 470R; R_Axial_DIN0207_L6.3mm_D2.5mm_P10.16mm_Horizontal; MPN MFR-25FBF52-470R
R13, R17: 22R; R_Axial_DIN0207_L6.3mm_D2.5mm_P10.16mm_Horizontal; MPN MFR-25FBF52-22R

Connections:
+5V: D1.1 (K), D3.1 (K), J1.1
/GPIO6: J2.1, R16.1
/GPIO12: J2.2, R12.1
/GPIO13: J2.3, R1.1
/GPIO16: J2.6, R2.1
/GPIO19: J2.5, R4.2
/GPIO20: J2.8, R3.1
/GPIO21: J2.10, R6.2
/GPIO26: J2.7, R5.2
/IDAC_A: J1.6, R11.1
/IDAC_B: J1.4, R15.1
/NODE_A: D1.2 (A), D2.1 (K), R7.2, R8.2, R9.2, R10.2, R11.2, R12.2, R13.1
/NODE_B: D3.2 (A), D4.1 (K), R14.2, R15.2, R16.2, R17.1
/N_HI: J1.11, R3.2, R6.1, R9.1
/N_LO: J1.7, R1.2, R4.1, R7.1
/N_MID: J1.9, R2.2, R5.1, R8.1
/PROBE_A: J3.1, R13.2
/PROBE_B: J3.2, R17.2
/SENSE_A: J1.5, R10.1
/SENSE_B: J1.3, R14.1
GND: D2.2 (A), D4.2 (A), J1.2, J1.13, J2.4, J2.9

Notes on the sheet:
Probe helper (docs/probe-helper-pi.md, tools/probe_ads1263.py). Plugs into the Waveshare High-Precision AD HAT's 13-way 3.5 mm screw terminal (J1) and takes 8 Pi GPIOs over a 10-way ribbon from the HAT's pass-through header (J2). Each range is a GPIO divider: top GPIO high + bottom GPIO low puts it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
AVDD
AVSS
IN0
IN1
IN2
IN3
IN4
IN5
IN6
IN7
IN8
IN9
COM
J1: 13 single pins cut from a 2.54 mm right-angle strip, soldered at 3.5 mm pitch on the bottom side. Order (Pi standard view): AVDD left ... COM right.
J2 pin n = Pi pin 30 + n: 10-way IDC ribbon (same-side crimp) to an IDC socket on the AD HAT's pass-through pins 31-40 (socket pin 1 on Pi pin 31).
lo range
mid range
hi range
D1-D4 clamp the probe nodes to GND and +5 V (AVDD). At the 10 M range the clamps' leakage adds to the nA signal: if R reads finite with the probes open, fit low-leakage DO-35 diodes (1N3595, BAS45A) for D1/D2.
J3: 1 = probe A (red), 2 = probe B (black). Any 5.0/5.08 mm 2-way terminal fits.

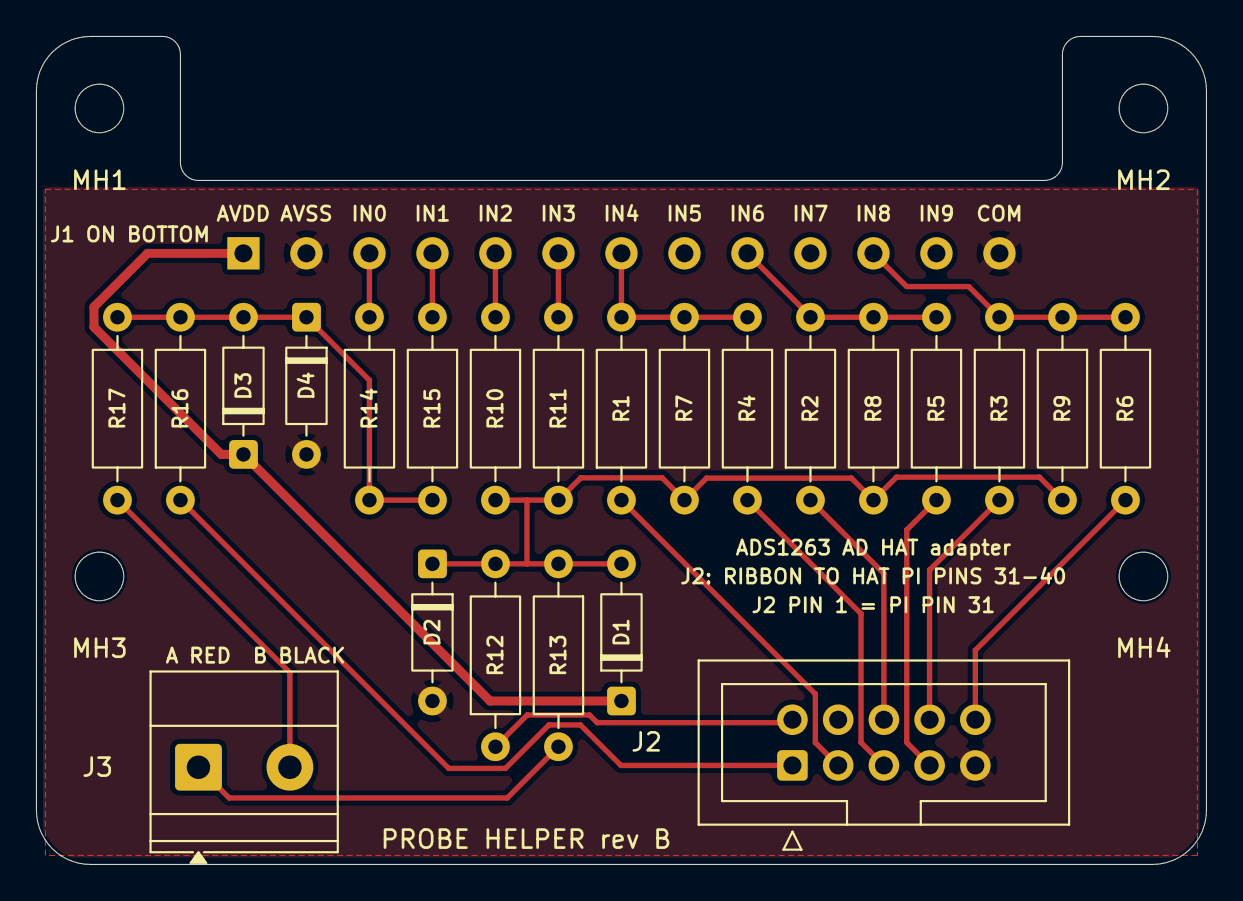
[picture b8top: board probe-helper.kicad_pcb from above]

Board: 2 copper layers, 65.0 x 46.0 mm, 28 parts (1 on the bottom side), 21 nets.

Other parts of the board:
MH1, MH2, MH3, MH4: MountingHole_2.7mm_M2.5
